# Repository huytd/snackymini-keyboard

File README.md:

# Snackymini Keyboard

<details>
<summary>See more about design and PCB layout</summary>

**QWERTY Layout:**

**Dvorak Layout:**

Inspired by MiniVan Arrow Layout http://www.keyboard-layout-editor.com/#/gists/174470794149140f43dd6c9b544c168c

**Schema:**

**PCB:**

**PCB render:**

</details>

## Parts
- 1x Teensy 3.2 with header pins
- 47x Cherry MX Switches (choose your color)
- 47x Key caps in various size
- 47x 1N4148 diodes

## How to use this repository?
First, you'll need to install [KiCad](http://kicad-pcb.org/), then you can open the PCB project in `hardware` folder to edit the PCB/Layout as you wish.

I have included the `snackymini-manufacturing-submission.zip` file containing all of the gerber files needed so you can send it to the manufacturer directly.

Ater having the PCB printed, you can use Arduino IDE (with Teensyduino installed) to compile the code in `firmware` folder, then upload it to your Teensy.

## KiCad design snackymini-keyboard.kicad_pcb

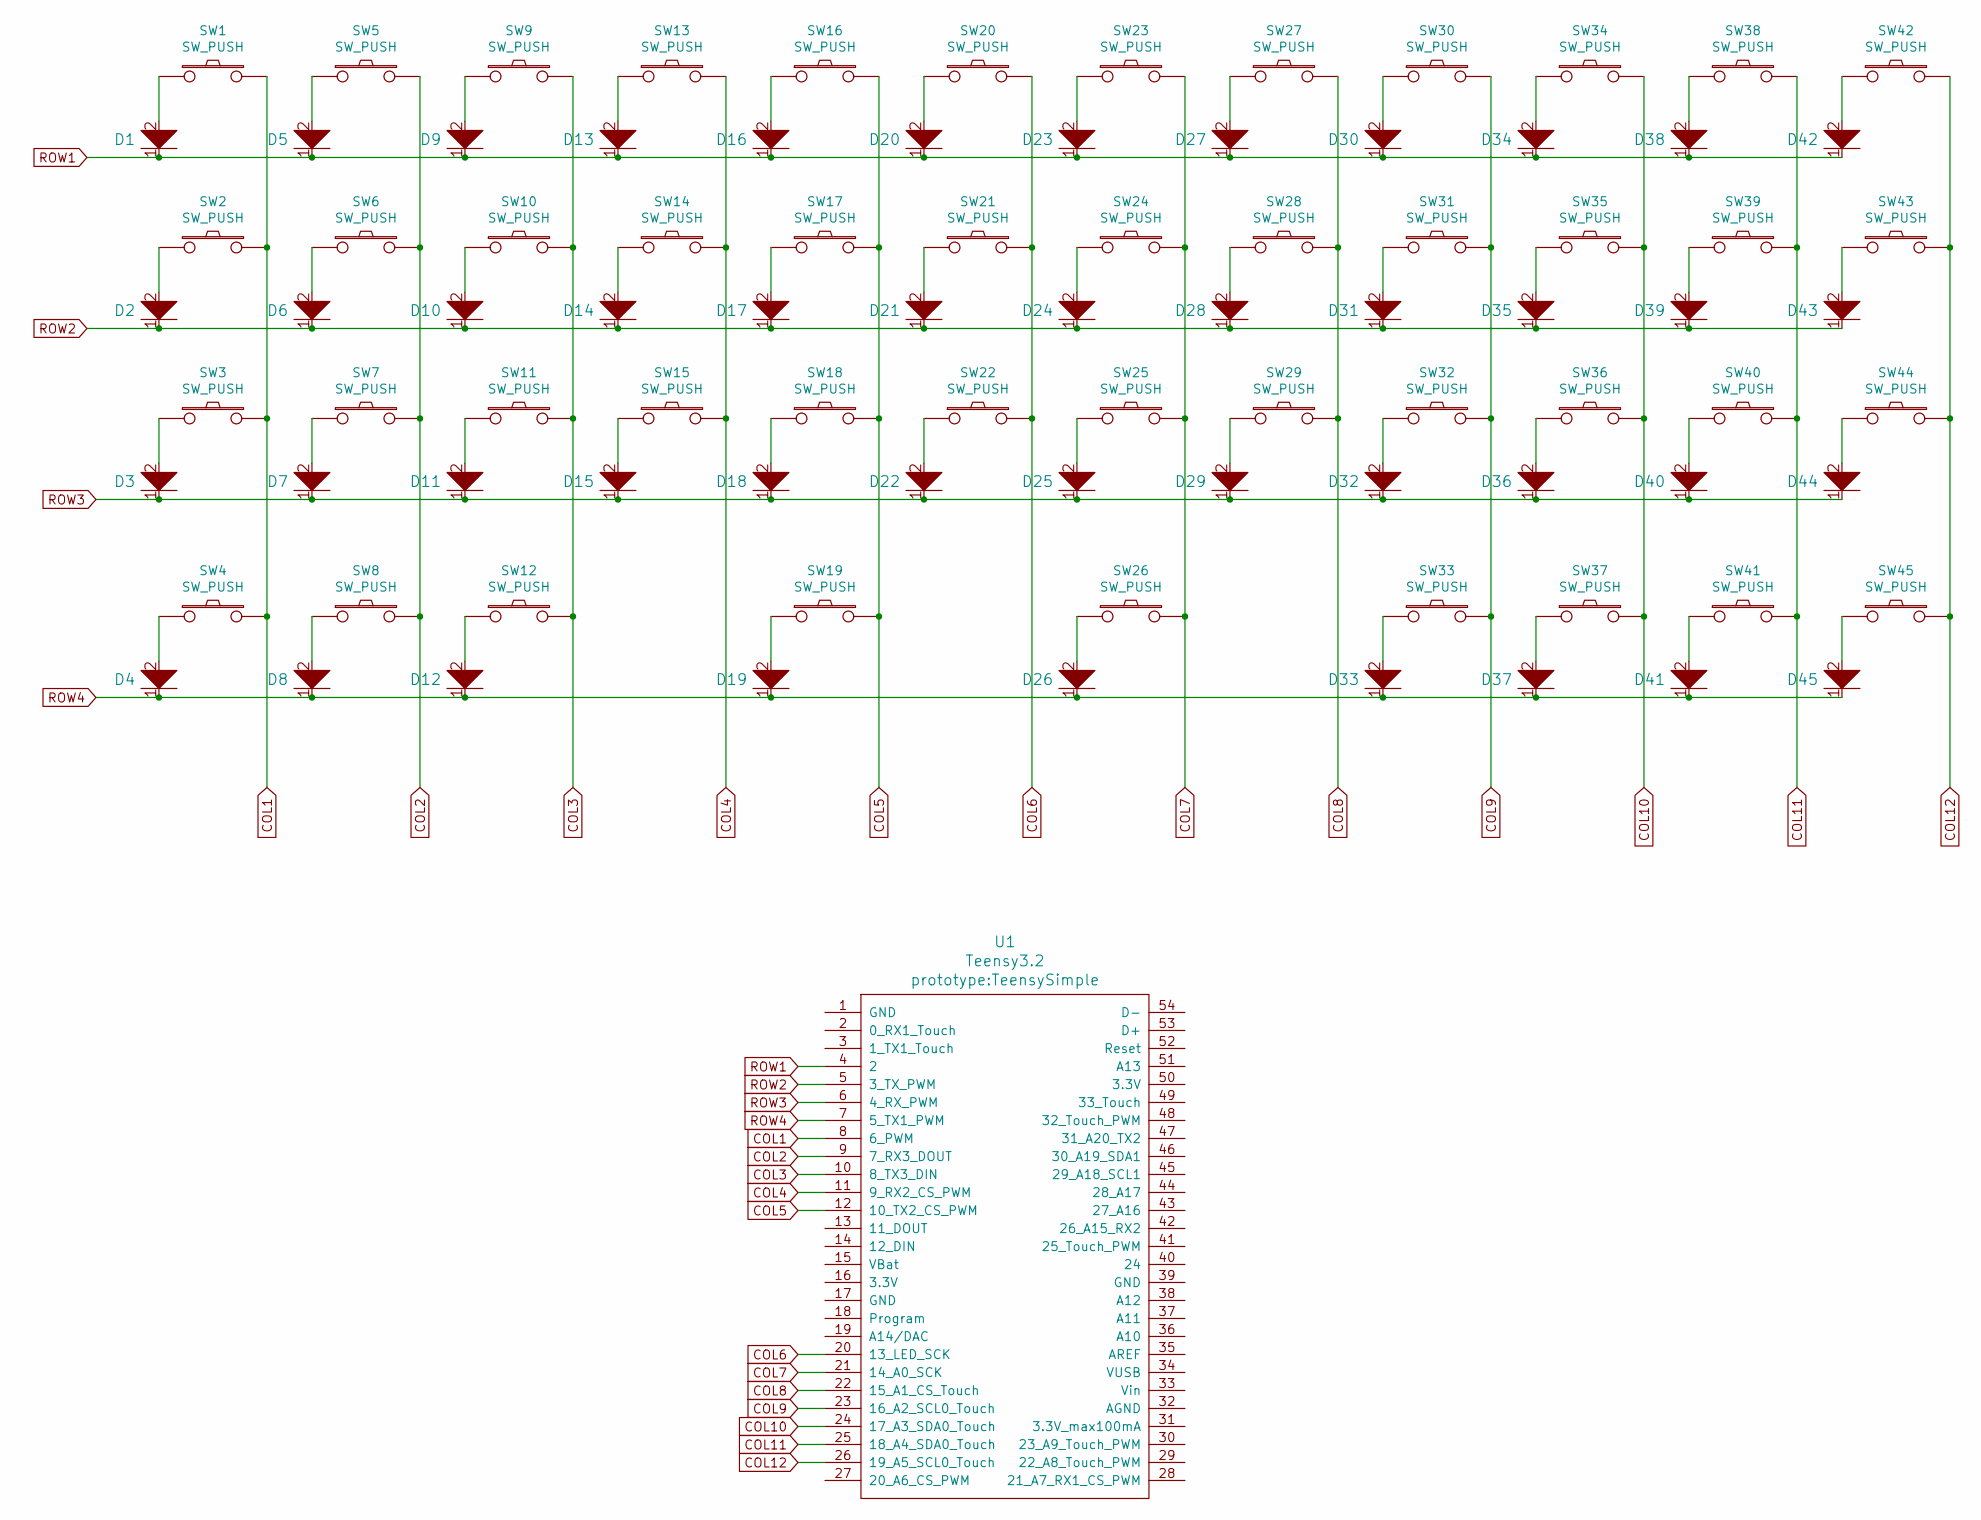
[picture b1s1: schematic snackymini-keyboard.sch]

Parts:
D1, D2, D3, D4, D5, D6, D7, D8, D9, D10, D11, D12, D13, D14, D15, D16, D17, D18, D19, D20, D21, D22, D23, D24, D25, D26, D27, D28, D29, D30, D31, D32, D33, D34, D35, D36, D37, D38, D39, D40, D41, D42, D43, D44, D45: D; D_axial
SW1, SW2, SW3, SW4, SW5, SW6, SW7, SW8, SW9, SW10, SW11, SW12, SW13, SW14, SW15, SW16, SW17, SW18, SW19, SW20, SW21, SW22, SW23, SW24, SW25, SW26, SW27, SW28, SW29, SW30, SW31, SW32, SW33, SW34, SW35, SW36, SW37, SW38, SW39, SW40, SW41, SW42, SW43, SW44, SW45: SW_PUSH; CHERRY_PLATE_100H
U1: Teensy3.2; TeensySimple

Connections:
COL1: SW1.2, SW2.2, SW3.2, SW4.2, U1.8 (6_PWM)
COL2: SW5.2, SW6.2, SW7.2, SW8.2, U1.9 (7_RX3_DOUT)
COL3: SW9.2, SW10.2, SW11.2, SW12.2, U1.10 (8_TX3_DIN)
COL4: SW13.2, SW14.2, SW15.2, U1.11 (9_RX2_CS_PWM)
COL5: SW16.2, SW17.2, SW18.2, SW19.2, U1.12 (10_TX2_CS_PWM)
COL6: SW20.2, SW21.2, SW22.2, U1.20 (13_LED_SCK)
COL7: SW23.2, SW24.2, SW25.2, SW26.2, U1.21 (14_A0_SCK)
COL8: SW27.2, SW28.2, SW29.2, U1.22 (15_A1_CS_Touch)
COL9: SW30.2, SW31.2, SW32.2, SW33.2, U1.23 (16_A2_SCL0_Touch)
COL10: SW34.2, SW35.2, SW36.2, SW37.2, U1.24 (17_A3_SDA0_Touch)
COL11: SW38.2, SW39.2, SW40.2, SW41.2, U1.25 (18_A4_SDA0_Touch)
COL12: SW42.2, SW43.2, SW44.2, SW45.2, U1.26 (19_A5_SCL0_Touch)
unnamed: D1.2, SW1.1
unnamed: D2.2, SW2.1
unnamed: D3.2, SW3.1
unnamed: D4.2, SW4.1
unnamed: D5.2, SW5.1
unnamed: D6.2, SW6.1
unnamed: D7.2, SW7.1
unnamed: D8.2, SW8.1
unnamed: D9.2, SW9.1
unnamed: D10.2, SW10.1
unnamed: D11.2, SW11.1
unnamed: D12.2, SW12.1
unnamed: D13.2, SW13.1
unnamed: D14.2, SW14.1
unnamed: D15.2, SW15.1
unnamed: D16.2, SW16.1
unnamed: D17.2, SW17.1
unnamed: D18.2, SW18.1
unnamed: D19.2, SW19.1
unnamed: D20.2, SW20.1
unnamed: D21.2, SW21.1
unnamed: D22.2, SW22.1
unnamed: D23.2, SW23.1
unnamed: D24.2, SW24.1
unnamed: D25.2, SW25.1
unnamed: D26.2, SW26.1
unnamed: D27.2, SW27.1
unnamed: D28.2, SW28.1
unnamed: D29.2, SW29.1
unnamed: D30.2, SW30.1
unnamed: D31.2, SW31.1
unnamed: D32.2, SW32.1
unnamed: D33.2, SW33.1
unnamed: D34.2, SW34.1
unnamed: D35.2, SW35.1
unnamed: D36.2, SW36.1
unnamed: D37.2, SW37.1
unnamed: D38.2, SW38.1
unnamed: D39.2, SW39.1
unnamed: D40.2, SW40.1
unnamed: D41.2, SW41.1
unnamed: D42.2, SW42.1
unnamed: D43.2, SW43.1
unnamed: D44.2, SW44.1
unnamed: D45.2, SW45.1
ROW1: D1.1, D5.1, D9.1, D13.1, D16.1, D20.1, D23.1, D27.1, D30.1, D34.1, D38.1, D42.1, U1.4 (2)
ROW2: D2.1, D6.1, D10.1, D14.1, D17.1, D21.1, D24.1, D28.1, D31.1, D35.1, D39.1, D43.1, U1.5 (3_TX_PWM)
ROW3: D3.1, D7.1, D11.1, D15.1, D18.1, D22.1, D25.1, D29.1, D32.1, D36.1, D40.1, D44.1, U1.6 (4_RX_PWM)
ROW4: D4.1, D8.1, D12.1, D19.1, D26.1, D33.1, D37.1, D41.1, D45.1, U1.7 (5_TX1_PWM)

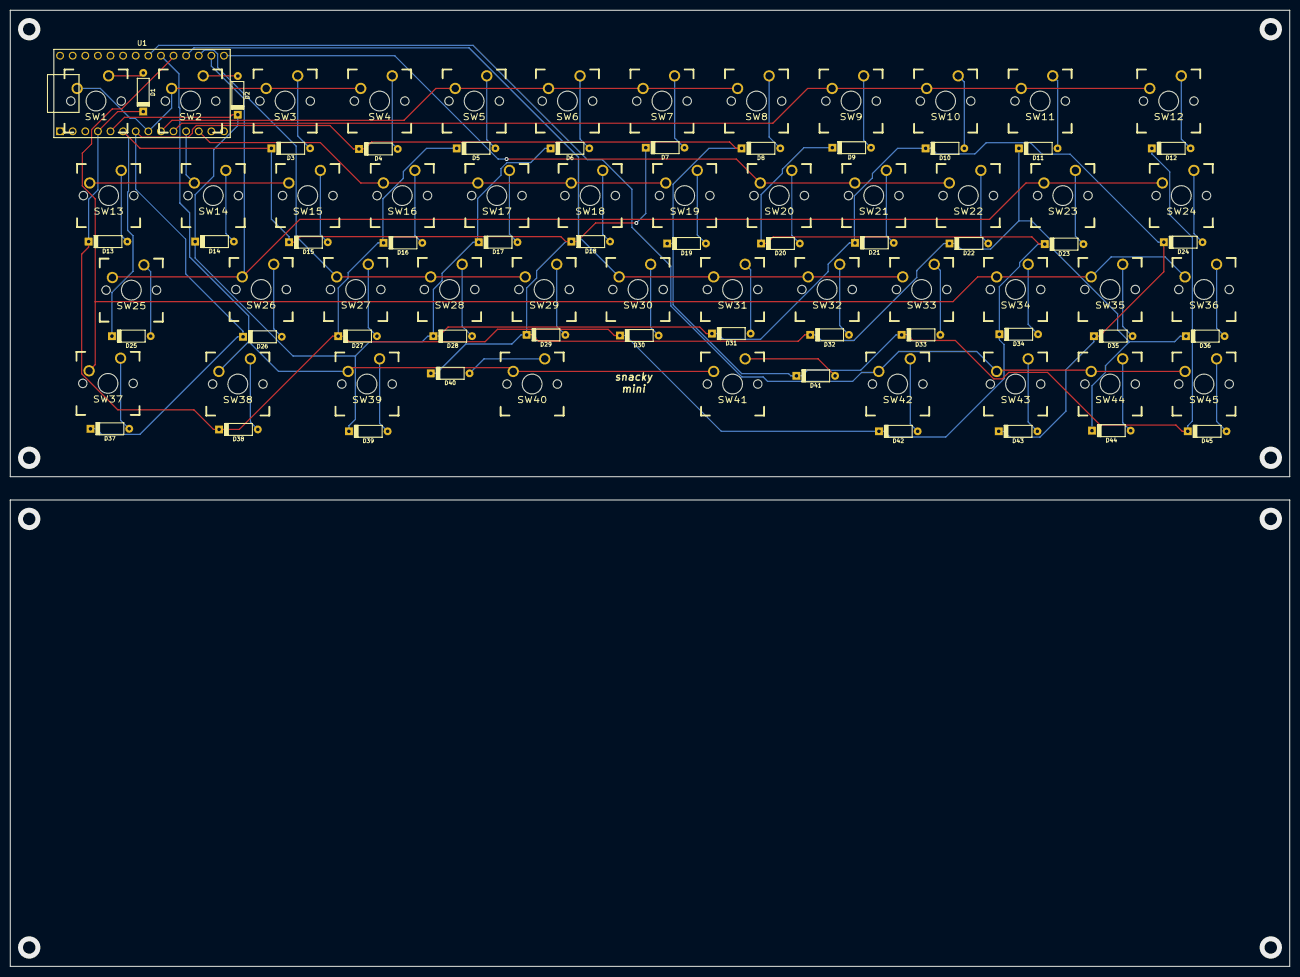
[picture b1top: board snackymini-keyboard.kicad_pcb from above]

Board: 2 copper layers, 257.8 x 94.0 mm, 91 parts (0 on the bottom side), 61 nets.

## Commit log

2018-12-23 Update layout and routing, add corner mount hole
2018-12-23 Update readme and screenshot
2018-12-24 Update layout
2019-01-30 Update PCB pinout
2019-02-04 Update final image
2019-02-06 Add firmware code
2019-02-06 Update keyboard scanning algorithm
2019-02-06 Re-organizing the project
2019-02-07 Remove some unused code and enhance the layout
2019-02-07 Fix issue keyboard could not send number 3 keys.
    The reason behind this is, I was using space character
    as a flag for empty key, it is also conflict with the
    number 3 keys which has the value of 0x20, also a space.
    LOL.
2019-02-07 Implement NKRO
    This implementation supports 6-keys roll over.
    Want more? hook up another keyboard to the usb
    port. LOL.
2019-02-07 Update keyboard layout image
2019-02-07 Refactoring and reformatting, also added a device name config
2019-02-07 Use spaces not tabs
2019-02-08 Add one more quote key, this one is better reach
2019-02-08 Oops, forgot to format the code
2019-02-21 Add some measurement
2019-02-21 Add some images
2019-02-21 Implement Dvorak support. Enabled by default.
2019-02-21 Dvorak Layout Tweak
2019-02-21 Add image for Dvorak layout
2019-08-05 Update keyboard layout
